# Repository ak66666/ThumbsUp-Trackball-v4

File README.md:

# ThumbsUp! Trackball v4

A PCB-based finger-operated trackball, inspired by Elecom EX-G left hand trackball, Ploopy Nano trackball, and my own ThumbsUp! Trackball v3.
 
Off-the-shelf ProMicro-style MCUs is considered: 
- nice!nano v2 (and clones) with ZMK-based firmware - wireless/wired/BT/dongle.

~~34 mm ball, same as in Elecom EX-G, or~~ 44 mm, or 52.5mm as in Elecom Huge, or 55mm balls.
57mm ball may work - sensor needs to be adjusted to provide 2.4 mm distance from the lens to the ball surface.

For bearings - uxcell 2.5mm Ceramic Bearing Balls, ZrO2 Zirconium Oxide Ball, again, the same as used to improve my Elecom trackballs.
Bearings to be implanted into PCBs, no 3D-printed ball shroud/holder.

A few buttons scattered on top of the boards, not sure about their bindings yet, so let's say 6 of them at least + 4 for reset/ZMK.Studio/BT Reset/BT Next.
I.e. let's keep the buttons of v3 for now.
(As of rev.2 there are 8 "large" buttons, 3 programmable and 1 reset low-profile buttons.)

Rev.2 with 55 mm Ball: 

Rev.1 with 44 mm Ball:

USB dongle (n!n in a case):

Other pictures in Photos folder.
 
# Firmware

Bluetooth/wired connection:
https://github.com/ak66666/zmk-config-trackball.v4

USB dongle:
https://github.com/ak66666/zmk-config-trackball.v4.dongle

# For sale on Etsy
 
https://www.etsy.com/ca/listing/4390959934/thumbsup-trackball-v4-44-or-525-or-55mm

# Assembly Instructions
https://thumbsupkeyboards.blogspot.com/2025/12/thumbsup-trackball-v4-assembly-step.html

# Parts List for DYI
https://github.com/ak66666/ThumbsUp-Trackball-v4/blob/main/Kicad/Trackball/Fabrication/Trackball%20v4%2C%20Parts%20for%20DYI%2C%20Costs.xlsx

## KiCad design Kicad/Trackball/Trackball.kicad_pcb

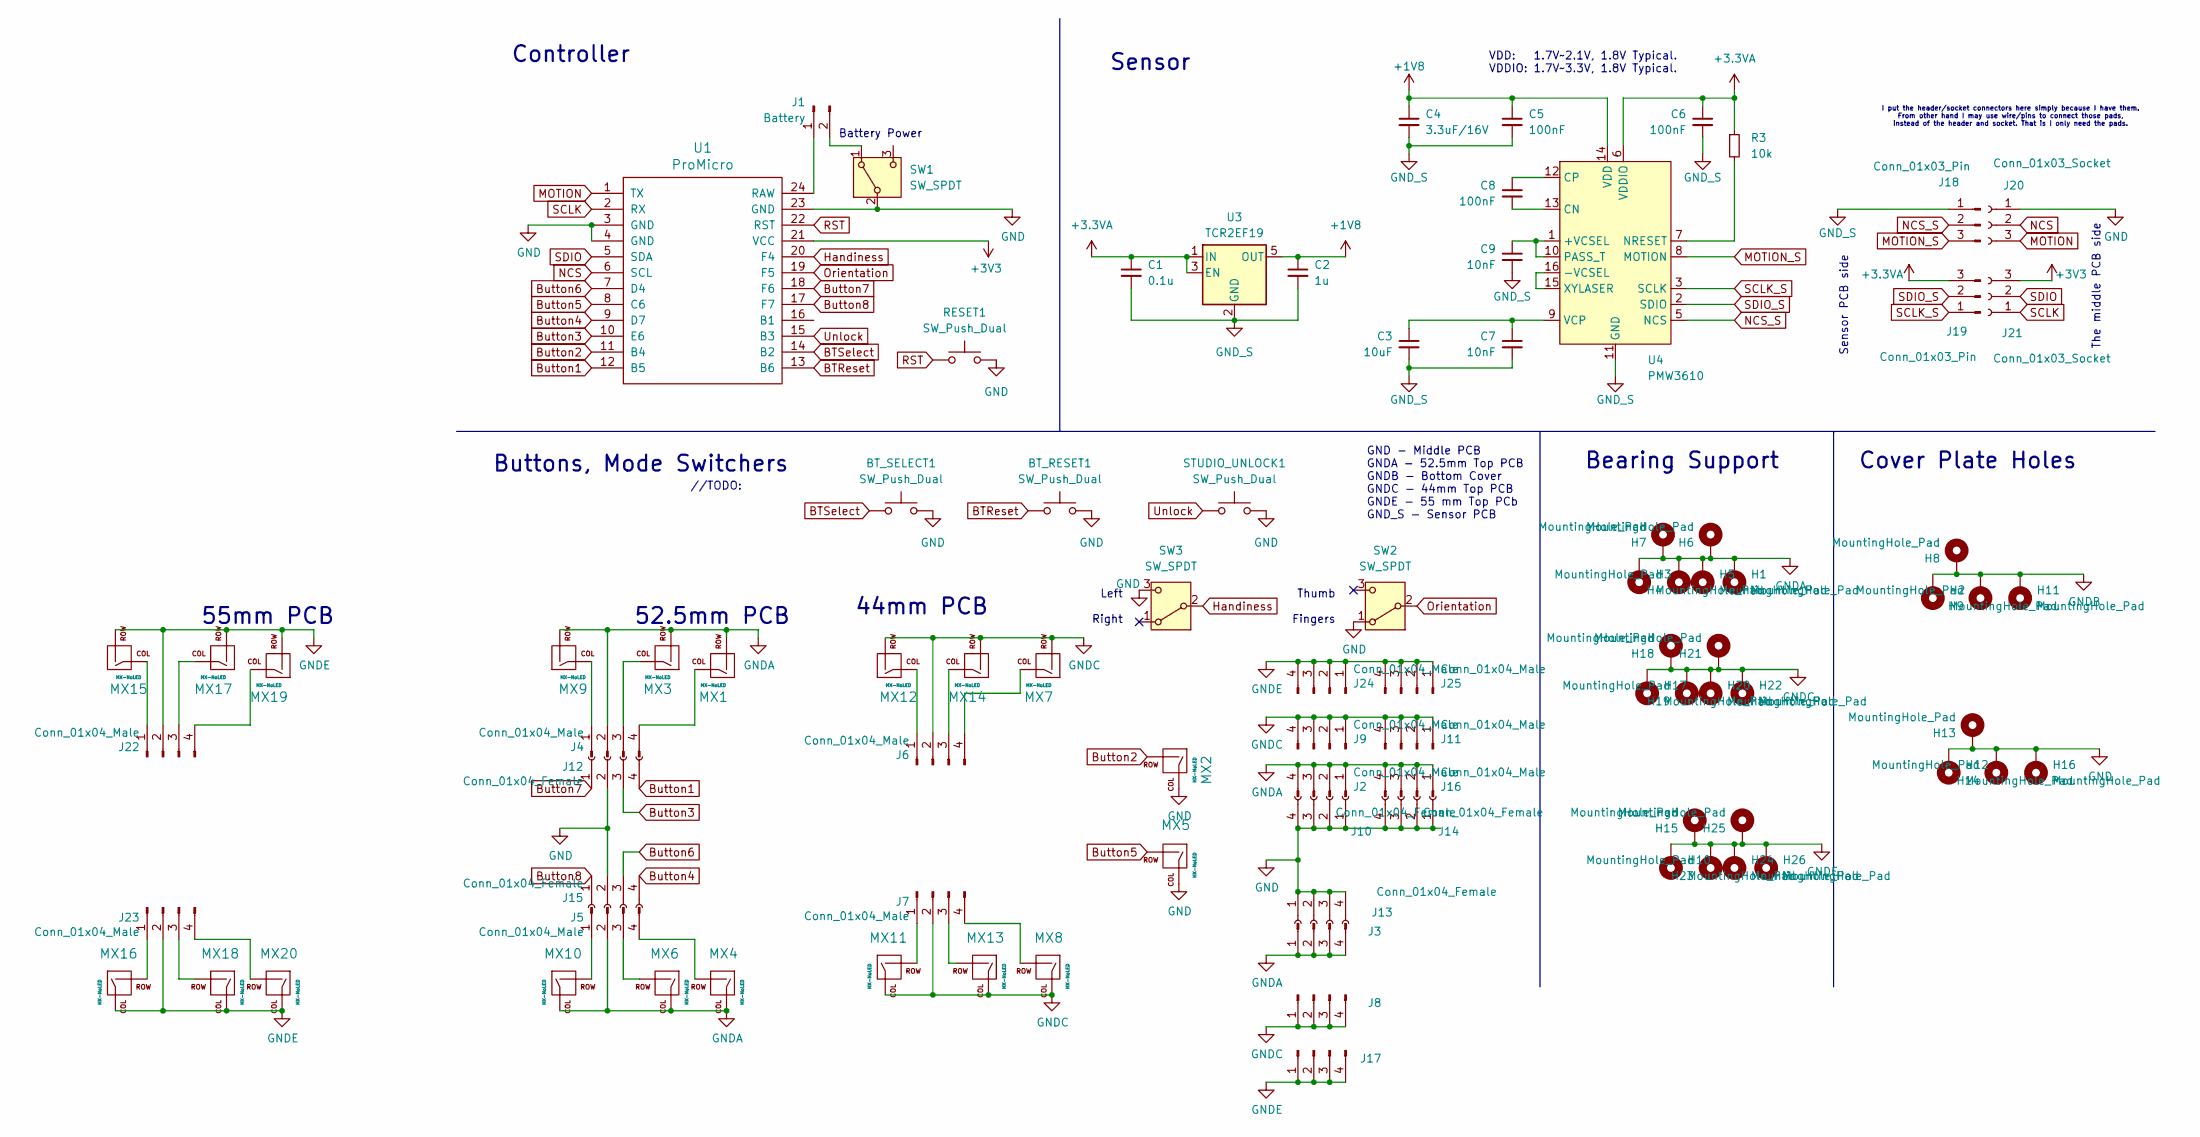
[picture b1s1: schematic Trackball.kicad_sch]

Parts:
BT_RESET1: SW_Push_Dual; SW_Push_1P1T_NO_CK_KSC6xxJ
BT_SELECT1: SW_Push_Dual; SW_Push_1P1T_NO_CK_KSC6xxJ
C1: 0.1u; C_0402_1005Metric
C2: 1u; C_0402_1005Metric
C3: 10uF; C_0402_1005Metric; MFR. Part # CL21A106KAYNNNE; JLCPCB Part # C15850
C4: 3.3uF/16V; C_0805_2012Metric; MFR. Part # TCC0805X7R335K250FT; JLCPCB Part # C7393948
C5, C6, C8: 100nF; C_0402_1005Metric; MFR. Part # CC0603KRX7R9BB104; JLCPCB Part # C14663
C7, C9: 10nF; C_0402_1005Metric; MFR. Part # 0603B103K500NT; JLCPCB Part # C57112
H1, H3, H4, H5, H6, H7, H10, H15, H17, H18, H19, H20, H21, H22, H23, H24, H25, H26: MountingHole_Pad; MountingHole_2.5mm_Pad
H2, H8, H9, H11, H12, H13, H14, H16: MountingHole_Pad; MountingHole_3.7mm_Pad
J1: Battery; PinHeader_1x02_P2.54mm_Vertical
J2, J3, J4, J5, J6, J7, J8, J9, J11, J16, J17, J22, J23, J24, J25: Conn_01x04_Male; PinHeader_1x04_P2.54mm_Vertical
J10, J12, J13, J14, J15: Conn_01x04_Female; PinSocket_1x04_P2.54mm_Vertical
J18, J19: Conn_01x03_Pin; PinHeader_1x03_P2.54mm_Vertical
J20, J21: Conn_01x03_Socket; PinSocket_1x03_P2.54mm_Vertical
MX1, MX2, MX3, MX4, MX5, MX6, MX7, MX8, MX9, MX10, MX11, MX12, MX13, MX14, MX15, MX16, MX17, MX18, MX19, MX20: MX-NoLED; Kailh_socket_PG1350
R3: 10k; R_0603_1608Metric; MFR. Part # 0603WAF1002T5E; JLCPCB Part # C25804
RESET1: SW_Push_Dual; SW_Push_1P1T_NO_CK_KSC6xxJ
STUDIO_UNLOCK1: SW_Push_Dual; SW_Push_1P1T_NO_CK_KSC6xxJ
SW1, SW2, SW3: SW_SPDT; 18252321
U1: ProMicro
U3: TCR2EF19; SOT-23-5
U4: PMW3610; PMW3610DM-SUDU 16Pin; MFR. Part # PMW3610DM-SUDU; JLCPCB Part # C42442560

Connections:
+1V8: C2.1, C4.1, C5.1, U3.5 (OUT), U4.14 (VDD)
+3.3VA: C1.1, C6.1, J19.3, R3.1, U3.1 (IN), U3.3 (EN), U4.6 (VDDIO)
+3V3: J21.3, U1.21 (VCC)
BTReset: BT_RESET1.1, U1.13 (B6)
BTSelect: BT_SELECT1.1, U1.14 (B2)
Button1: J12.4, U1.12 (B5)
Button2: MX2.2 (ROW), U1.11 (B4)
Button3: J12.3, U1.10 (E6)
Button4: J15.4, U1.9 (D7)
Button5: MX5.2 (ROW), U1.8 (C6)
Button6: J15.3, U1.7 (D4)
Button7: J12.1, U1.18 (F6)
Button8: J15.1, U1.17 (F7)
GND: BT_RESET1.2, BT_SELECT1.2, H12.1, H13.1, H14.1, H16.1, J10.1, J10.2, J10.3, J10.4, J12.2, J13.1, J13.2, J13.3, J13.4, J14.1, J14.2, J14.3, J14.4, J15.2, J20.1, MX2.1 (COL), MX5.1 (COL), RESET1.2, STUDIO_UNLOCK1.2, SW1.2 (B), SW2.1 (A), SW3.1 (A), SW3.3 (C), U1.3 (GND), U1.4 (GND), U1.23 (GND)
GNDA: H1.1, H3.1, H4.1, H5.1, H6.1, H7.1, J2.1, J2.2, J2.3, J2.4, J3.1, J3.2, J3.3, J3.4, J4.2, J5.2, J16.1, J16.2, J16.3, J16.4, MX1.2 (ROW), MX3.2 (ROW), MX4.1 (COL), MX6.1 (COL), MX9.2 (ROW), MX10.1 (COL)
GNDB: H2.1, H8.1, H9.1, H11.1
GNDC: H17.1, H18.1, H19.1, H20.1, H21.1, H22.1, J6.2, J7.2, J8.1, J8.2, J8.3, J8.4, J9.1, J9.2, J9.3, J9.4, J11.1, J11.2, J11.3, J11.4, MX7.2 (ROW), MX8.1 (COL), MX11.1 (COL), MX12.2 (ROW), MX13.1 (COL), MX14.2 (ROW)
GNDE: H10.1, H15.1, H23.1, H24.1, H25.1, H26.1, J17.1, J17.2, J17.3, J17.4, J22.2, J23.2, J24.1, J24.2, J24.3, J24.4, J25.1, J25.2, J25.3, J25.4, MX15.2 (ROW), MX16.1 (COL), MX17.2 (ROW), MX18.1 (COL), MX19.2 (ROW), MX20.1 (COL)
GND_S: C1.2, C2.2, C3.2, C4.2, C5.2, C6.2, C7.2, C9.2, J18.1, U3.2 (GND), U4.11 (GND)
Handiness: SW3.2 (B), U1.20 (F4)
MOTION: J20.3, U1.1 (TX)
MOTION_S: J18.3, U4.8 (MOTION)
NCS: J20.2, U1.6 (SCL)
NCS_S: J18.2, U4.5 (NCS)
unnamed: J1.1, U1.24 (RAW)
unnamed: J1.2, SW1.1 (A)
unnamed: J4.1, MX9.1 (COL)
unnamed: J4.3, MX3.1 (COL)
unnamed: J4.4, MX1.1 (COL)
unnamed: J5.1, MX10.2 (ROW)
unnamed: J5.3, MX6.2 (ROW)
unnamed: J5.4, MX4.2 (ROW)
unnamed: J6.1, MX12.1 (COL)
unnamed: J6.3, MX14.1 (COL)
unnamed: J6.4, MX7.1 (COL)
unnamed: J7.1, MX11.2 (ROW)
unnamed: J7.3, MX13.2 (ROW)
unnamed: J7.4, MX8.2 (ROW)
unnamed: J22.1, MX15.1 (COL)
unnamed: J22.3, MX17.1 (COL)
unnamed: J22.4, MX19.1 (COL)
unnamed: J23.1, MX16.2 (ROW)
unnamed: J23.3, MX18.2 (ROW)
unnamed: J23.4, MX20.2 (ROW)
unnamed: C9.1, U4.1 (+VCSEL), U4.10 (PASS_T)
unnamed: U4.15 (XYLASER), U4.16 (-VCSEL)
unnamed: C8.2, U4.13 (CN)
unnamed: C8.1, U4.12 (CP)
unnamed: R3.2, U4.7 (NRESET)
unnamed: C3.1, C7.1, U4.9 (VCP)
Orientation: SW2.2 (B), U1.19 (F5)
RST: RESET1.1, U1.22 (RST)
SCLK: J21.1, U1.2 (RX)
SCLK_S: J19.1, U4.3 (SCLK)
SDIO: J21.2, U1.5 (SDA)
SDIO_S: J19.2, U4.2 (SDIO)
Unlock: STUDIO_UNLOCK1.1, U1.15 (B3)

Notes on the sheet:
//TODO:
VDD: 1.7V~2.1V, 1.8V Typical. VDDIO: 1.7V~3.3V, 1.8V Typical.
Battery Power
I put the header/socket connectors here simply because I have them. From other hand I may use wire/pins to connect those pads, instead of the header and socket. That is I only need the pads.
Cover Plate Holes
GND - Middle PCB GNDA - 52.5mm Top PCB GNDB - Bottom Cover GNDC - 44mm Top PCB GNDE - 55 mm Top PCb GND_S - Sensor PCB
The middle PCB side
Sensor PCB side
44mm PCB
Thumb Fingers
52.5mm PCB
Buttons, Mode Switchers
Controller
Bearing Support
55mm PCB
Sensor
Left Right

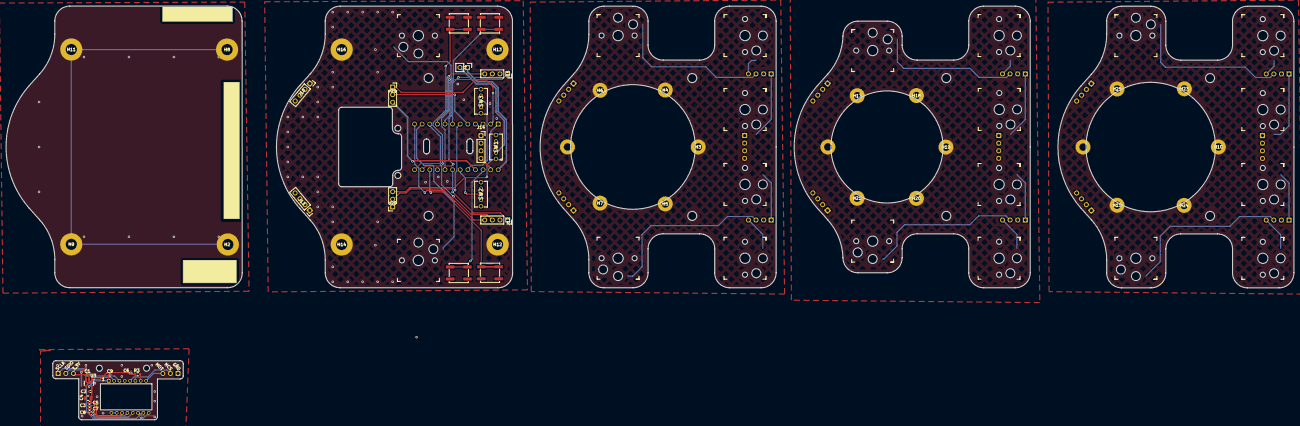
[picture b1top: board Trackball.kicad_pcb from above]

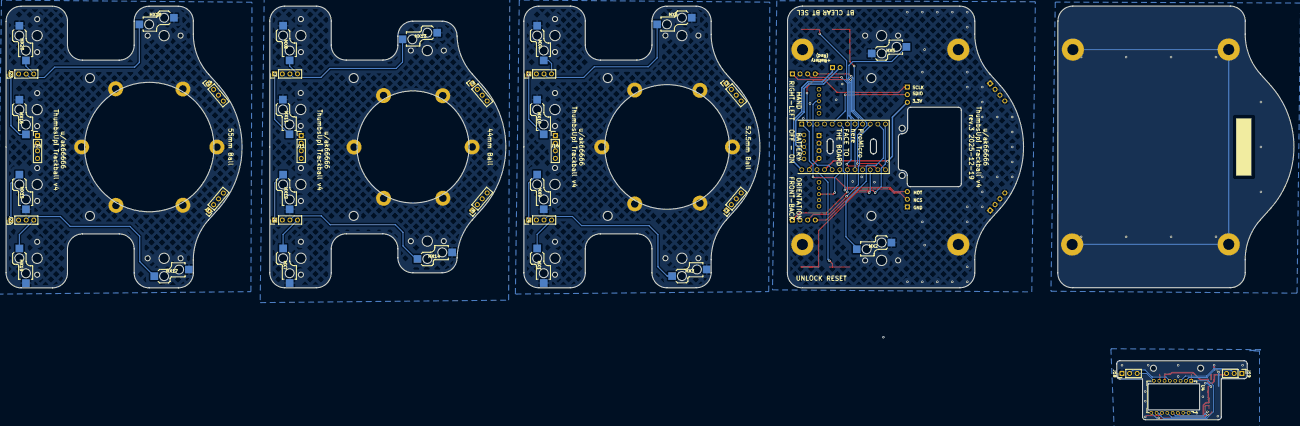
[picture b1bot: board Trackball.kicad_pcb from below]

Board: 2 copper layers, 429.8 x 138.1 mm, 91 parts (18 on the bottom side), 57 nets.

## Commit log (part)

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2025-09-19 B4: Project started.
2025-09-19 B4: PCB outlines defined. To do: correct schematics - swap male/female sockets, move the buttons to appropriate PCBs. Add 44mm base and the bottom cover.
2025-09-19 B4: Base, Cover, 52.5 mm ball platform ready. TODO: add 44mm platform.
2025-09-19 B4: Added 44mm platform. TODO: Prepare Gerbers for fabrication.
2025-09-19 B4: Corrected labels on the protective cover. TODO: Prepare Gerbers for fabrication.
2025-09-19 B4: Gerbers prepared.
2025-09-19 B4: Renamed Gerbers to distinguish them from v3
2025-09-19 B4: Trying to hoax JLC to think the bottom plate is small - added pad holes instead of simple holes.
2025-09-19 B4: Corrected the labels that were covered by the new pads.
2025-10-01 B4: Corrected the PCBs, added two more keys. TODO: add 55mm top deck.
2025-10-02 B4: Added 55mm top PCB, moved the buttons around, reduced the overall outline. TODO: lay out the wiring.
2025-10-03 B4: Wired all the layers. TODO: generate Gerbers.
2025-10-03 B4: Flipped n!n to the back side, facing up - to the board.
2025-10-03 B4: Regenerated Gerbers for the middle and bottom decks, sent for manufacturing.
2025-10-03 Update README.md
    Added 55mm ball, removed 34mm mention
2025-10-03 B4: Added photos of rev.1 device.
2025-10-19 B4: Added more photos.
2025-10-20 Update README with firmware connection links
    Added links for Bluetooth and USB dongle firmware.
2025-12-05 B3: Replaced the dongle files.
2025-12-16 B4: Added DYI part list.
2025-12-16 Added DYI parts list, references to store.
2025-12-16 B4: Added dongle pictures
2025-12-18 B4: Corrected orientation switch labels, moved the battery tie-down holes to its center. TODO: recreate Gerbers.
2025-12-18 B4: Recreated gerbers for the two bottom PCBs, ordered them 2025-12-18.
2025-12-19 B4: Moved the ball size label to a place readable in assembled unit.
2025-12-19 B4: Added copper layer under the labels on the two bottom PCBs. TODO: regenerate all Gerbers.
2026-03-26 Revise assembly instructions for Trackball v4
    Updated assembly instructions and removed outdated link.
2026-05-27 B4: Put the correct firmware.
